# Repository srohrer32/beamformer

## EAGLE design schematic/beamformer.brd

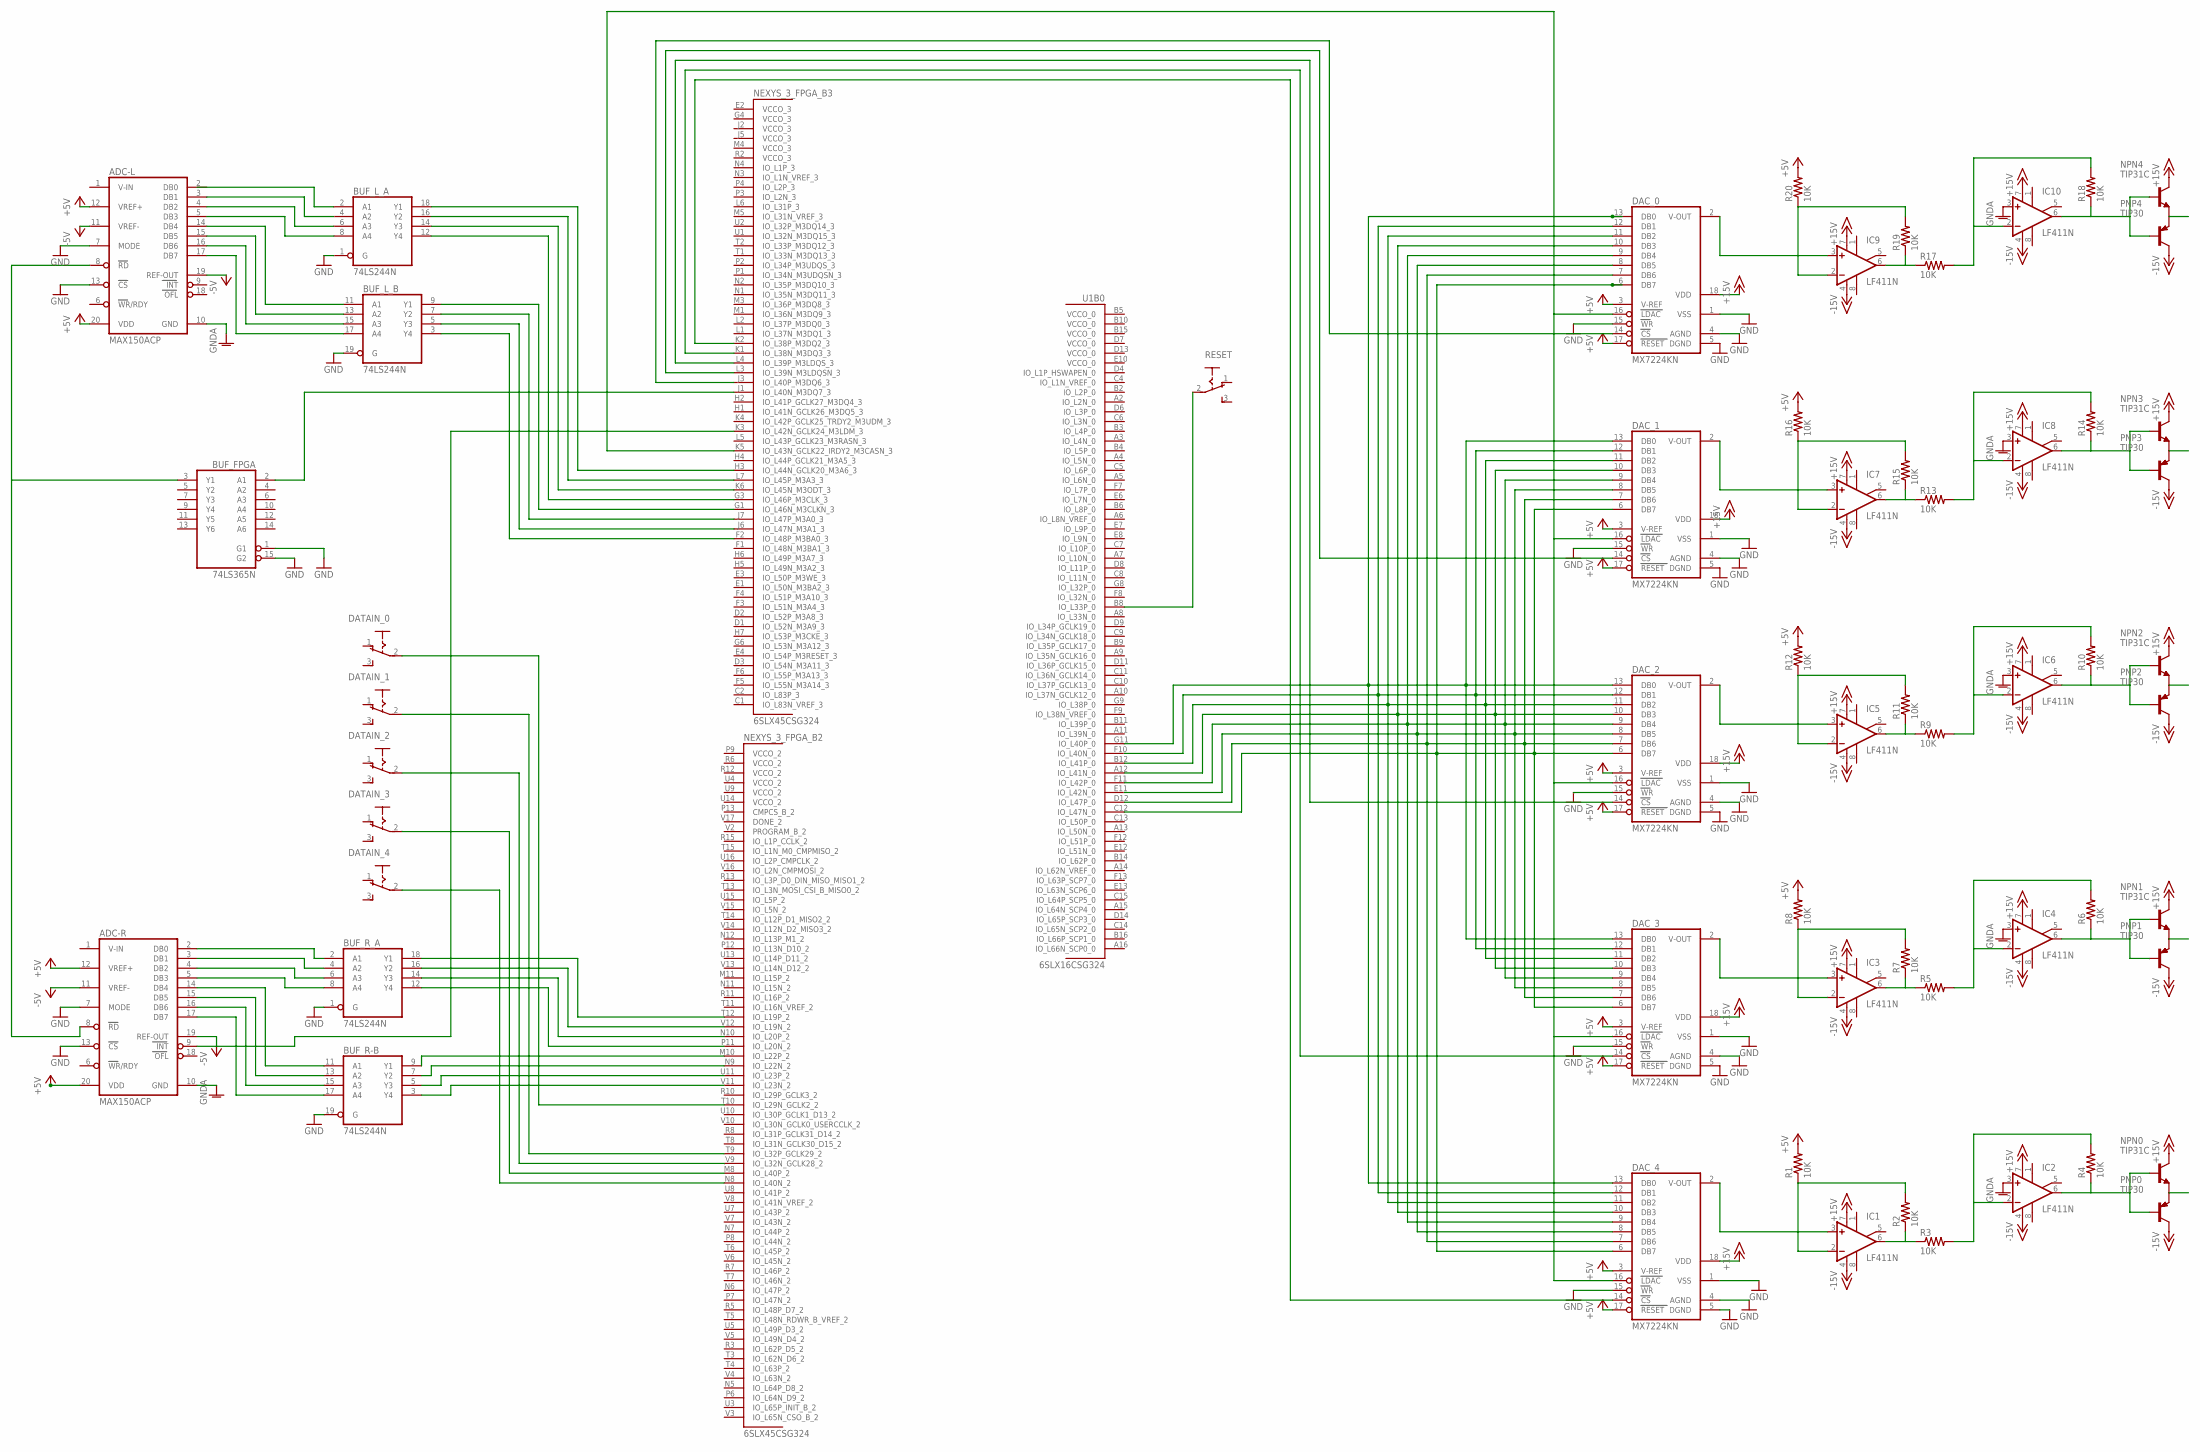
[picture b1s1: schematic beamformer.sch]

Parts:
ADC-L: MAX150ACP; DIL20
ADC-R: MAX150ACP; DIL20
BUF_FPGA: 74LS365N; DIL16
BUF_L_: 74LS244N; DIL20
BUF_R-: 74LS244N; DIL20
BUF_R_: 74LS244N; DIL20
DAC_0, DAC_1, DAC_2, DAC_3, DAC_4: MX7224KN; DIL18
DATAIN_0, DATAIN_1, DATAIN_2, DATAIN_3, DATAIN_4: M251
IC1, IC2, IC3, IC4, IC5, IC6, IC7, IC8, IC9, IC10: LF411N; DIL08
NEXYS_3_FPGA_: 6SLX45CSG324; CS324
NPN0, NPN1, NPN2, NPN3, NPN4: TIP31C; TO220
PNP0, PNP1, PNP2, PNP3, PNP4: TIP30; TO220
R1, R2, R3, R4, R5, R6, R7, R8, R9, R10, R11, R12, R13, R14, R15, R16, R17, R18, R19, R20: 10K; 0204/7
RESET: M251
U1: 6SLX16CSG324; CS324

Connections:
+5V: ADC-L.12 (VREF+), ADC-L.20 (VDD), ADC-R.12 (VREF+), ADC-R.20 (VDD), DAC_0.3 (V-REF), DAC_0.17 (RESET), DAC_1.3 (V-REF), DAC_1.17 (RESET), DAC_2.3 (V-REF), DAC_2.17 (RESET), DAC_3.3 (V-REF), DAC_3.17 (RESET), DAC_4.3 (V-REF), DAC_4.17 (RESET), R1.2, R8.2, R12.2, R16.2, R20.2
+15V: DAC_0.18 (VDD), DAC_1.18 (VDD), DAC_2.18 (VDD), DAC_3.18 (VDD), DAC_4.18 (VDD), IC1.7 (V+), IC2.7 (V+), IC3.7 (V+), IC4.7 (V+), IC5.7 (V+), IC6.7 (V+), IC7.7 (V+), IC8.7 (V+), IC9.7 (V+), IC10.7 (V+), NPN0.2 (C), NPN1.2 (C), NPN2.2 (C), NPN3.2 (C), NPN4.2 (C)
-5V: ADC-L.11 (VREF-), ADC-L.19 (REF-OUT), ADC-R.11 (VREF-), ADC-R.19 (REF-OUT)
-15V: IC1.4 (V-), IC2.4 (V-), IC3.4 (V-), IC4.4 (V-), IC5.4 (V-), IC6.4 (V-), IC7.4 (V-), IC8.4 (V-), IC9.4 (V-), IC10.4 (V-), PNP0.2 (C), PNP1.2 (C), PNP2.2 (C), PNP3.2 (C), PNP4.2 (C)
GND: ADC-L.7 (MODE), ADC-L.13 (CS), ADC-R.7 (MODE), ADC-R.13 (CS), BUF_FPGA.1 (G1), BUF_FPGA.8 (GND), BUF_FPGA.15 (G2), BUF_L_.1 (G), BUF_L_.10 (GND), BUF_L_.19 (G), BUF_R-.10 (GND), BUF_R-.19 (G), BUF_R_.1 (G), BUF_R_.10 (GND), DAC_0.1 (VSS), DAC_0.4 (AGND), DAC_0.5 (DGND), DAC_0.15 (WR), DAC_1.1 (VSS), DAC_1.4 (AGND), DAC_1.5 (DGND), DAC_1.15 (WR), DAC_2.1 (VSS), DAC_2.4 (AGND), DAC_2.5 (DGND), DAC_2.15 (WR), DAC_3.1 (VSS), DAC_3.4 (AGND), DAC_3.5 (DGND), DAC_3.15 (WR), DAC_4.1 (VSS), DAC_4.4 (AGND), DAC_4.5 (DGND), DAC_4.15 (WR), NEXYS_3_FPGA_.A1 (GND), NEXYS_3_FPGA_.A18 (GND), NEXYS_3_FPGA_.B7 (GND), NEXYS_3_FPGA_.B13 (GND), NEXYS_3_FPGA_.C3 (GND), NEXYS_3_FPGA_.C16 (GND), NEXYS_3_FPGA_.D5 (GND), NEXYS_3_FPGA_.D10 (GND), NEXYS_3_FPGA_.E15 (GND), NEXYS_3_FPGA_.G2 (GND), NEXYS_3_FPGA_.G5 (GND), NEXYS_3_FPGA_.G12 (GND), NEXYS_3_FPGA_.G17 (GND), NEXYS_3_FPGA_.H8 (GND), NEXYS_3_FPGA_.H10 (GND), NEXYS_3_FPGA_.J4 (GND), NEXYS_3_FPGA_.J9 (GND), NEXYS_3_FPGA_.J11 (GND), NEXYS_3_FPGA_.J15 (GND), NEXYS_3_FPGA_.K8 (GND), NEXYS_3_FPGA_.K10 (GND), NEXYS_3_FPGA_.L9 (GND), NEXYS_3_FPGA_.L11 (GND), NEXYS_3_FPGA_.M2 (GND), NEXYS_3_FPGA_.M6 (GND), NEXYS_3_FPGA_.M17 (GND), NEXYS_3_FPGA_.N13 (GND), NEXYS_3_FPGA_.R1 (GND), NEXYS_3_FPGA_.R4 (GND), NEXYS_3_FPGA_.R9 (GND), NEXYS_3_FPGA_.R14 (GND), NEXYS_3_FPGA_.R18 (GND), NEXYS_3_FPGA_.T16 (GND), NEXYS_3_FPGA_.U6 (GND), NEXYS_3_FPGA_.U12 (GND), NEXYS_3_FPGA_.V1 (GND), NEXYS_3_FPGA_.V18 (GND), U1.A1 (GND), U1.A18 (GND), U1.B7 (GND), U1.B13 (GND), U1.C3 (GND), U1.C16 (GND), U1.D5 (GND), U1.D10 (GND), U1.E15 (GND), U1.G2 (GND), U1.G5 (GND), U1.G12 (GND), U1.G17 (GND), U1.H8 (GND), U1.H10 (GND), U1.J4 (GND), U1.J9 (GND), U1.J11 (GND), U1.J15 (GND), U1.K8 (GND), U1.K10 (GND), U1.L9 (GND), U1.L11 (GND), U1.M2 (GND), U1.M6 (GND), U1.M17 (GND), U1.N13 (GND), U1.R1 (GND), U1.R4 (GND), U1.R9 (GND), U1.R14 (GND), U1.R18 (GND), U1.T16 (GND), U1.U6 (GND), U1.U12 (GND), U1.V1 (GND), U1.V18 (GND)
GNDA: ADC-L.10 (GND), ADC-R.10 (GND), IC2.3 (+IN), IC4.3 (+IN), IC6.3 (+IN), IC8.3 (+IN), IC10.3 (+IN)
unnamed: ADC-L.3 (DB1), BUF_L_.4 (A2)
unnamed: ADC-L.4 (DB2), BUF_L_.6 (A3)
unnamed: ADC-L.5 (DB3), BUF_L_.8 (A4)
unnamed: ADC-L.14 (DB4), BUF_L_.11 (A1)
unnamed: ADC-L.15 (DB5), BUF_L_.13 (A2)
unnamed: ADC-L.16 (DB6), BUF_L_.15 (A3)
unnamed: ADC-L.17 (DB7), BUF_L_.17 (A4)
unnamed: ADC-L.8 (RD), ADC-R.8 (RD), BUF_FPGA.3 (Y1)
unnamed: ADC-R.2 (DB0), BUF_R_.2 (A1)
unnamed: ADC-R.3 (DB1), BUF_R_.4 (A2)
unnamed: ADC-R.4 (DB2), BUF_R_.6 (A3)
unnamed: ADC-R.5 (DB3), BUF_R_.8 (A4)
unnamed: ADC-R.14 (DB4), BUF_R-.11 (A1)
unnamed: ADC-R.15 (DB5), BUF_R-.13 (A2)
unnamed: ADC-R.16 (DB6), BUF_R-.15 (A3)
unnamed: ADC-R.17 (DB7), BUF_R-.17 (A4)
unnamed: ADC-R.9 (INT), NEXYS_3_FPGA_.K3 (IO_L42N_GCLK24_M3LDM_3)
unnamed: BUF_FPGA.2 (A1), NEXYS_3_FPGA_.J1 (IO_L40N_M3DQ7_3)
unnamed: DATAIN_0.2, NEXYS_3_FPGA_.T10 (IO_L29N_GCLK2_2)
unnamed: DATAIN_1.2, NEXYS_3_FPGA_.T9 (IO_L32P_GCLK29_2)
unnamed: DATAIN_2.2, NEXYS_3_FPGA_.V9 (IO_L32N_GCLK28_2)
unnamed: DATAIN_3.2, NEXYS_3_FPGA_.M8 (IO_L40P_2)
unnamed: DATAIN_4.2, NEXYS_3_FPGA_.N8 (IO_L40N_2)
unnamed: RESET.2, U1.B8 (IO_L33P_0)
unnamed: BUF_L_.18 (Y1), NEXYS_3_FPGA_.H3 (IO_L44N_GCLK20_M3A6_3)
unnamed: BUF_L_.16 (Y2), NEXYS_3_FPGA_.L7 (IO_L45P_M3A3_3)
unnamed: BUF_L_.14 (Y3), NEXYS_3_FPGA_.K6 (IO_L45N_M3ODT_3)
unnamed: BUF_L_.12 (Y4), NEXYS_3_FPGA_.G3 (IO_L46P_M3CLK_3)
unnamed: BUF_L_.9 (Y1), NEXYS_3_FPGA_.G1 (IO_L46N_M3CLKN_3)
unnamed: BUF_L_.7 (Y2), NEXYS_3_FPGA_.J7 (IO_L47P_M3A0_3)
unnamed: BUF_L_.5 (Y3), NEXYS_3_FPGA_.J6 (IO_L47N_M3A1_3)
unnamed: BUF_L_.3 (Y4), NEXYS_3_FPGA_.F2 (IO_L48P_M3BA0_3)
unnamed: BUF_R_.18 (Y1), NEXYS_3_FPGA_.T12 (IO_L19P_2)
unnamed: BUF_R_.16 (Y2), NEXYS_3_FPGA_.V12 (IO_L19N_2)
unnamed: BUF_R_.14 (Y3), NEXYS_3_FPGA_.N10 (IO_L20P_2)
unnamed: BUF_R_.12 (Y4), NEXYS_3_FPGA_.P11 (IO_L20N_2)
unnamed: BUF_R-.9 (Y1), NEXYS_3_FPGA_.M10 (IO_L22P_2)
unnamed: BUF_R-.7 (Y2), NEXYS_3_FPGA_.N9 (IO_L22N_2)
unnamed: BUF_R-.5 (Y3), NEXYS_3_FPGA_.U11 (IO_L23P_2)
unnamed: BUF_R-.3 (Y4), NEXYS_3_FPGA_.V11 (IO_L23N_2)
unnamed: DAC_0.13 (DB0), DAC_1.13 (DB0), DAC_2.13 (DB0), DAC_3.13 (DB0), DAC_4.13 (DB0), U1.G11 (IO_L40P_0)
unnamed: DAC_0.12 (DB1), DAC_1.12 (DB1), DAC_2.12 (DB1), DAC_3.12 (DB1), DAC_4.12 (DB1), U1.F10 (IO_L40N_0)
unnamed: DAC_0.11 (DB2), DAC_1.11 (DB2), DAC_2.11 (DB2), DAC_3.11 (DB2), DAC_4.11 (DB2), U1.B12 (IO_L41P_0)
unnamed: DAC_0.10 (DB3), DAC_1.10 (DB3), DAC_2.10 (DB3), DAC_3.10 (DB3), DAC_4.10 (DB3), U1.A12 (IO_L41N_0)
unnamed: DAC_0.9 (DB4), DAC_1.9 (DB4), DAC_2.9 (DB4), DAC_3.9 (DB4), DAC_4.9 (DB4), U1.F11 (IO_L42P_0)
unnamed: DAC_0.8 (DB5), DAC_1.8 (DB5), DAC_2.8 (DB5), DAC_3.8 (DB5), DAC_4.8 (DB5), U1.E11 (IO_L42N_0)
unnamed: DAC_0.7 (DB6), DAC_1.7 (DB6), DAC_2.7 (DB6), DAC_3.7 (DB6), DAC_4.7 (DB6), U1.D12 (IO_L47P_0)
unnamed: DAC_0.6 (DB7), DAC_1.6 (DB7), DAC_2.6 (DB7), DAC_3.6 (DB7), DAC_4.6 (DB7), U1.C12 (IO_L47N_0)
unnamed: DAC_0.14 (CS), NEXYS_3_FPGA_.J3 (IO_L40P_M3DQ6_3)
unnamed: DAC_0.16 (LDAC), DAC_1.16 (LDAC), DAC_2.16 (LDAC), DAC_3.16 (LDAC), DAC_4.16 (LDAC), NEXYS_3_FPGA_.K5 (IO_L43N_GCLK22_IRDY2_M3CASN_3)
unnamed: NPN0.3 (E), PNP0.3 (E)
unnamed: DAC_4.2 (V-OUT), IC1.3 (+IN)
unnamed: DAC_3.14 (CS), NEXYS_3_FPGA_.K1 (IO_L38N_M3DQ3_3)
unnamed: IC2.6 (OUT), NPN0.1 (B), PNP0.1 (B), R4.1
unnamed: DAC_4.14 (CS), NEXYS_3_FPGA_.K2 (IO_L38P_M3DQ2_3)
unnamed: IC2.2 (-IN), R3.2, R4.2
unnamed: DAC_2.14 (CS), NEXYS_3_FPGA_.L4 (IO_L39P_M3LDQS_3)
unnamed: DAC_1.14 (CS), NEXYS_3_FPGA_.L3 (IO_L39N_M3LDQSN_3)
unnamed: IC1.6 (OUT), R2.1, R3.1
unnamed: IC1.2 (-IN), R1.1, R2.2
unnamed: DAC_3.2 (V-OUT), IC3.3 (+IN)
unnamed: NPN1.3 (E), PNP1.3 (E)
unnamed: IC4.6 (OUT), NPN1.1 (B), PNP1.1 (B), R6.1
unnamed: IC4.2 (-IN), R5.2, R6.2
unnamed: IC3.2 (-IN), R7.2, R8.1
unnamed: IC3.6 (OUT), R5.1, R7.1
unnamed: DAC_2.2 (V-OUT), IC5.3 (+IN)
unnamed: NPN2.3 (E), PNP2.3 (E)
unnamed: IC6.6 (OUT), NPN2.1 (B), PNP2.1 (B), R10.1
unnamed: IC6.2 (-IN), R9.2, R10.2
unnamed: IC5.2 (-IN), R11.2, R12.1
unnamed: IC5.6 (OUT), R9.1, R11.1
unnamed: DAC_1.2 (V-OUT), IC7.3 (+IN)
unnamed: NPN3.3 (E), PNP3.3 (E)
unnamed: IC8.6 (OUT), NPN3.1 (B), PNP3.1 (B), R14.1
unnamed: IC8.2 (-IN), R13.2, R14.2
unnamed: IC7.2 (-IN), R15.2, R16.1
unnamed: IC7.6 (OUT), R13.1, R15.1
unnamed: DAC_0.2 (V-OUT), IC9.3 (+IN)
unnamed: NPN4.3 (E), PNP4.3 (E)
unnamed: IC10.6 (OUT), NPN4.1 (B), PNP4.1 (B), R18.1
unnamed: IC10.2 (-IN), R17.2, R18.2
unnamed: IC9.2 (-IN), R19.2, R20.1
unnamed: IC9.6 (OUT), R17.1, R19.1
VCC: BUF_FPGA.16 (VCC), BUF_L_.20 (VCC), BUF_R-.20 (VCC), BUF_R_.20 (VCC)

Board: 2 copper layers, 59 parts (0 on the bottom side), 91 nets, no tracks yet.
